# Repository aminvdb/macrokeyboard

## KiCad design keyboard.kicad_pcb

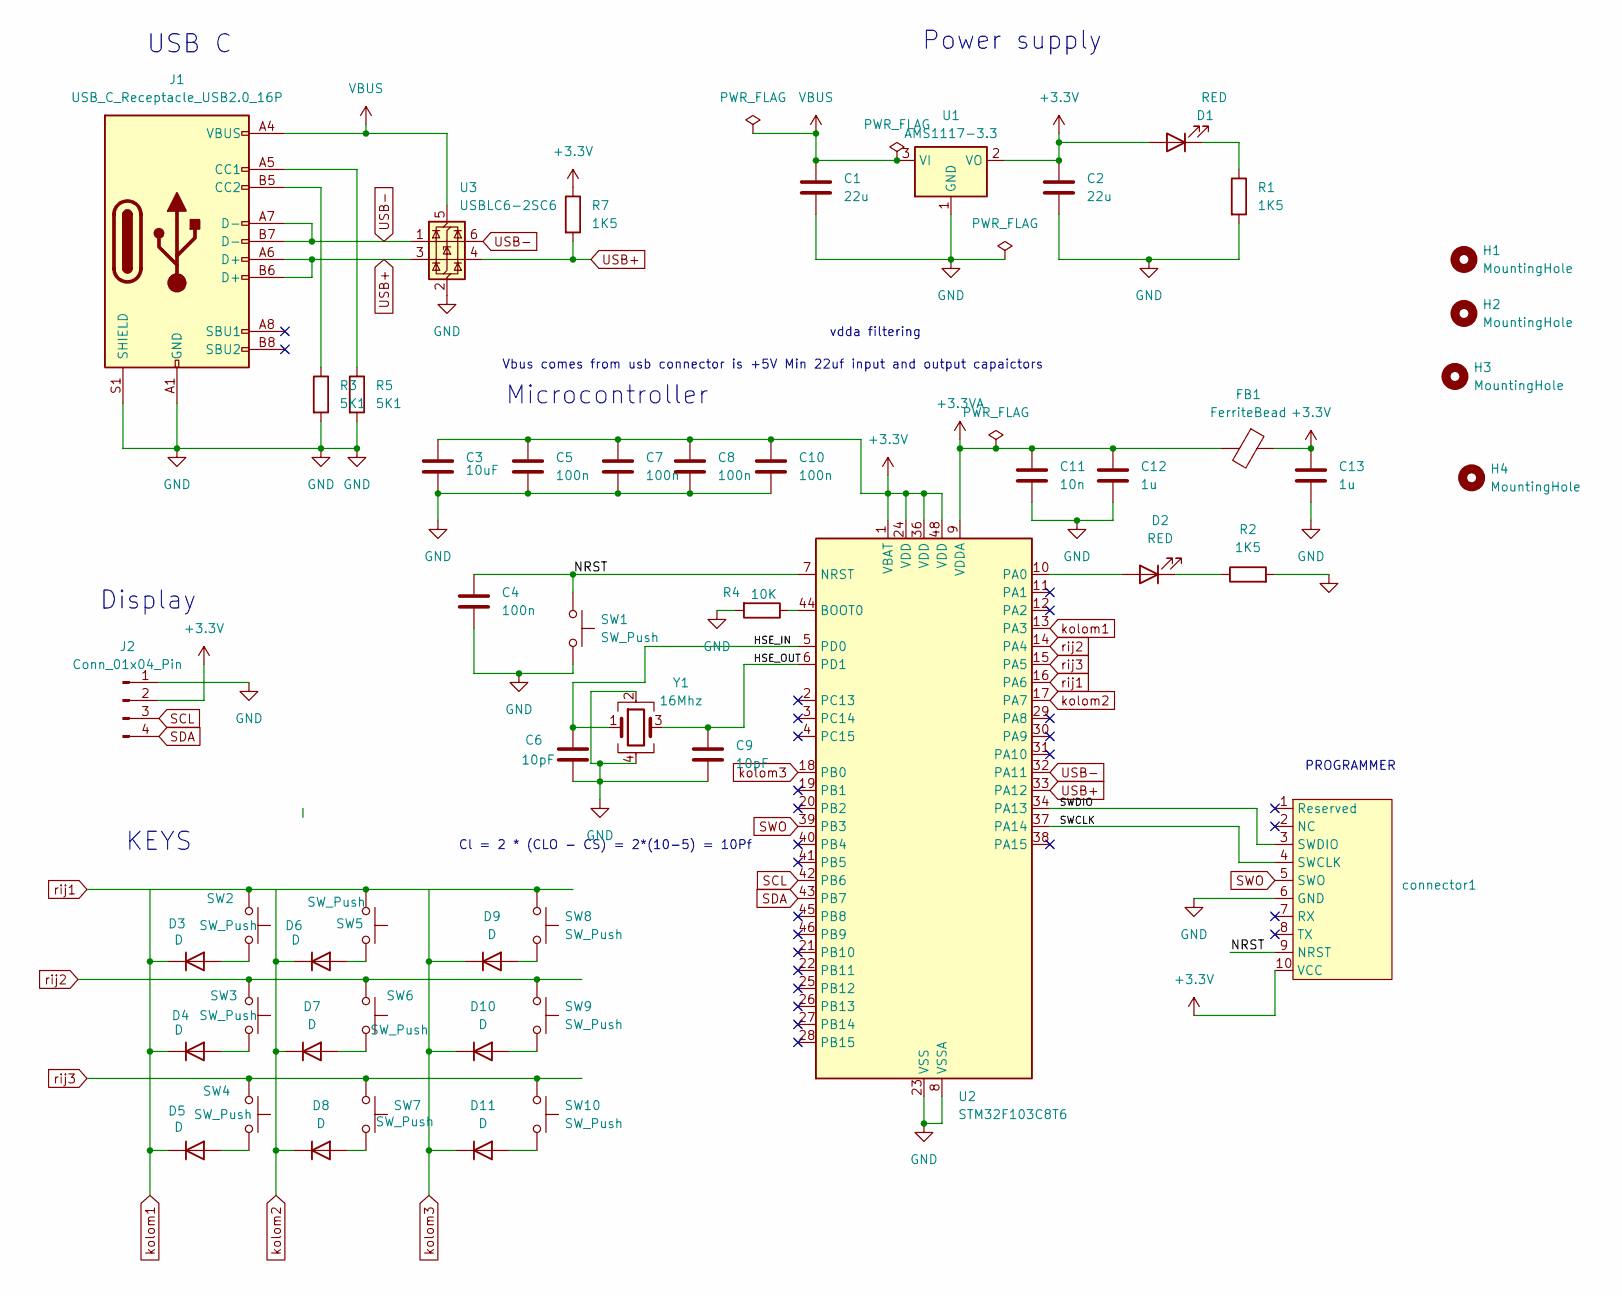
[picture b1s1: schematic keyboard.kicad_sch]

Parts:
C1, C2: 22u; C_0603_1608Metric
C3: 10uF; C_0603_1608Metric
C4, C5, C7, C8, C10: 100n; C_0603_1608Metric
C6, C9: 10pF; C_0603_1608Metric
C11: 10n; C_0603_1608Metric
C12, C13: 1u; C_0603_1608Metric
D1, D2: RED; LED_0603_1608Metric
D3, D4, D5, D6, D7, D8, D9, D10, D11: D; D_0603_1608Metric
FB1: FerriteBead; L_0603_1608Metric
H1, H2, H3, H4: MountingHole; MountingHole_2.1mm
J1: USB_C_Receptacle_USB2.0_16P; USB_C_Receptacle_GCT_USB4105-xx-A_16P_TopMnt_Horizontal
J2: Conn_01x04_Pin; PinHeader_1x04_P2.54mm_Vertical
R1, R2: 1K5; R_0402_1005Metric
R3, R5: 5K1; R_0603_1608Metric
R4: 10K; R_0603_1608Metric
R7: 1K5; R_0603_1608Metric
SW1: SW_Push; SW_SPST_TL3305B
SW2, SW3, SW4, SW5, SW6, SW7, SW8, SW9, SW10: SW_Push; Kailh_socket_MX
U1: AMS1117-3.3; SOT-223-3_TabPin2
U2: STM32F103C8T6; LQFP-48_7x7mm_P0.5mm
U3: USBLC6-2SC6; SOT-23-6
Y1: 16Mhz; Crystal_SMD_3225-4Pin_3.2x2.5mm
connector1: Open Ended Card Edge

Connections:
+3.3V: C2.1, C3.1, C5.1, C7.1, C8.1, C10.1, C13.1, D1.2 (A), FB1.1, J2.2, R7.1, U1.2 (VO), U2.1 (VBAT), U2.24 (VDD), U2.36 (VDD), U2.48 (VDD), connector1.10 (VCC)
+3.3VA: C11.1, C12.1, FB1.2, U2.9 (VDDA)
/HSE_IN: C6.1, U2.5 (PD0), Y1.1
/HSE_OUT: C9.1, U2.6 (PD1), Y1.3
/NRST: C4.1, SW1.1, U2.7 (NRST), connector1.9 (NRST)
/SWCLK: U2.37 (PA14), connector1.4 (SWCLK)
/SWDIO: U2.34 (PA13), connector1.3 (SWDIO)
GND: C1.2, C2.2, C3.2, C4.2, C5.2, C6.2, C7.2, C8.2, C9.2, C10.2, C11.2, C12.2, C13.2, J1.A1 (GND), J1.A12 (GND), J1.B1 (GND), J1.B12 (GND), J1.S1 (SHIELD), J2.1, R1.2, R2.2, R3.2, R4.2, R5.2, SW1.2, U1.1 (GND), U2.8 (VSSA), U2.23 (VSS), U2.35 (VSS), U2.47 (VSS), U3.2 (GND), Y1.2, Y1.4, connector1.6 (GND)
unnamed: D1.1 (K), R1.1
unnamed: D2.2 (A), U2.10 (PA0)
unnamed: D2.1 (K), R2.1
unnamed: D3.2 (A), SW2.2
unnamed: D4.2 (A), SW3.2
unnamed: D5.2 (A), SW4.2
unnamed: D6.2 (A), SW5.2
unnamed: D7.2 (A), SW6.2
unnamed: D8.2 (A), SW7.2
unnamed: D9.2 (A), SW8.2
unnamed: D10.2 (A), SW9.2
unnamed: D11.2 (A), SW10.2
unnamed: J1.A5 (CC1), R5.1
unnamed: J1.B5 (CC2), R3.1
unnamed: R4.1, U2.44 (BOOT0)
SCL: J2.3, U2.42 (PB6)
SDA: J2.4, U2.43 (PB7)
SWO: U2.39 (PB3), connector1.5 (SWO)
USB+: J1.A6 (D+), J1.B6 (D+), R7.2, U2.33 (PA12), U3.3 (I/O2), U3.4 (I/O2)
USB-: J1.A7 (D-), J1.B7 (D-), U2.32 (PA11), U3.1 (I/O1), U3.6 (I/O1)
VBUS: C1.1, J1.A4 (VBUS), J1.A9 (VBUS), J1.B4 (VBUS), J1.B9 (VBUS), U1.3 (VI), U3.5 (VBUS)
kolom1: D3.1 (K), D4.1 (K), D5.1 (K), U2.13 (PA3)
kolom2: D6.1 (K), D7.1 (K), D8.1 (K), U2.17 (PA7)
kolom3: D9.1 (K), D10.1 (K), D11.1 (K), U2.18 (PB0)
rij1: SW2.1, SW5.1, SW8.1, U2.16 (PA6)
rij2: SW3.1, SW6.1, SW9.1, U2.14 (PA4)
rij3: SW4.1, SW7.1, SW10.1, U2.15 (PA5)

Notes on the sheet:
KEYS
Power supply
Cl = 2 * (CLO - CS) = 2*(10-5) = 10Pf
vdda filtering
PROGRAMMER
USB C
Vbus comes from usb connector is +5V Min 22uf input and output capaictors
Microcontroller
Display

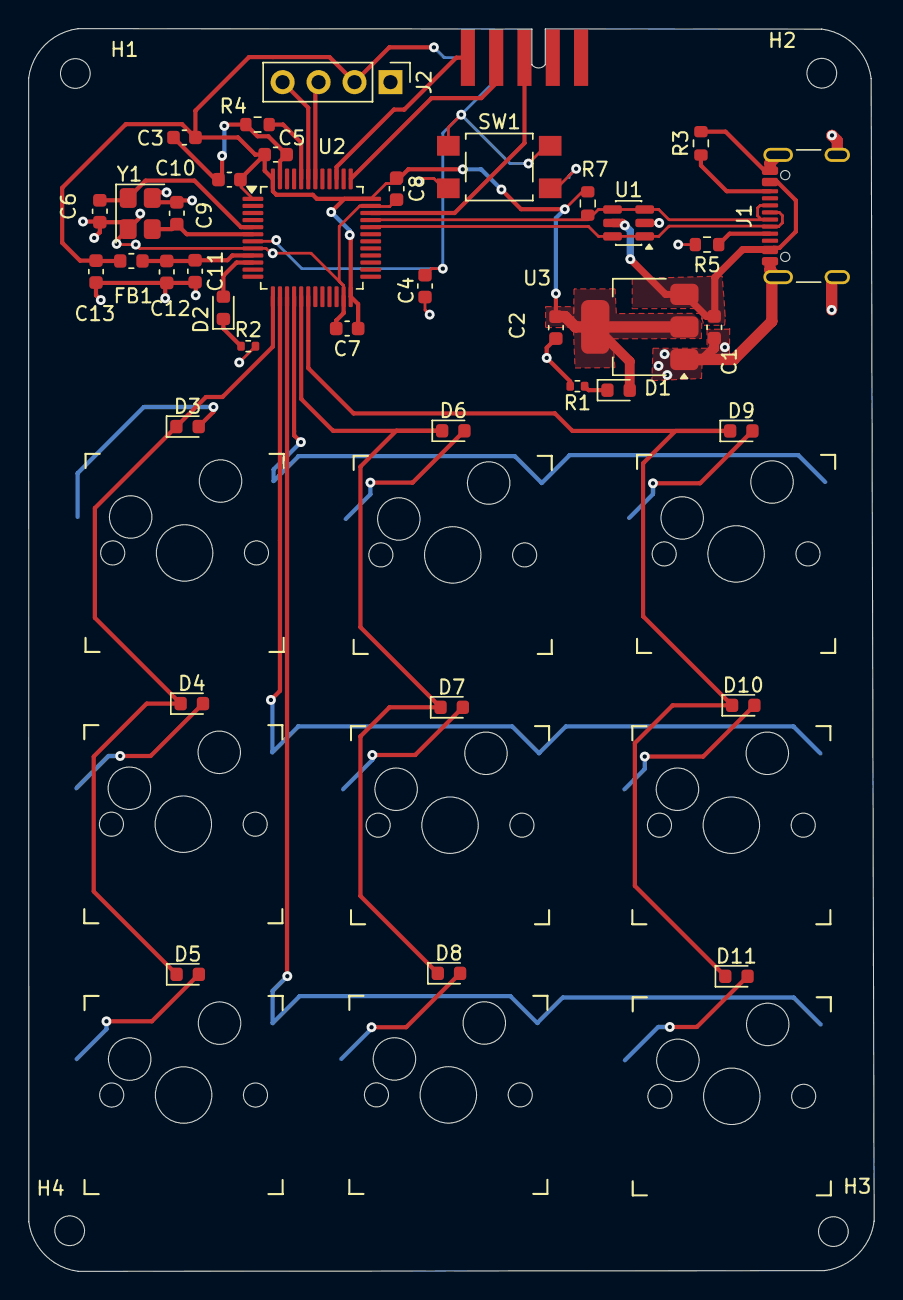
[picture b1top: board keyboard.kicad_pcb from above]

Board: 2 copper layers, 59.7 x 87.8 mm, 53 parts (0 on the bottom side), 35 nets.

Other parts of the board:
H3#2: MountingHole; MountingHole_2.1mm

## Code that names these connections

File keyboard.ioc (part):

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Mcu.Name=STM32F103C(8-B)Tx
Mcu.Package=LQFP48
Mcu.UserName=STM32F103C8Tx
PA11.Mode=Device
PA11.Signal=USB_DM
PA12.Mode=Device
PA12.Signal=USB_DP
PA13.Mode=Trace_Asynchronous_SW
PA13.Signal=SYS_JTMS-SWDIO
PA14.Mode=Trace_Asynchronous_SW
PA14.Signal=SYS_JTCK-SWCLK
PA3.GPIOParameters=GPIO_Label
PA3.GPIO_Label=kolom1
PA3.Signal=GPIO_Output
PA4.GPIOParameters=GPIO_PuPd,GPIO_Label
PA4.GPIO_Label=rij2
PA4.GPIO_PuPd=GPIO_PULLUP
PA4.Signal=GPIO_Input
PA5.GPIOParameters=GPIO_PuPd,GPIO_Label
PA5.GPIO_Label=rij3
PA5.GPIO_PuPd=GPIO_PULLUP
PA5.Signal=GPIO_Input
PA6.GPIOParameters=GPIO_PuPd,GPIO_Label
PA6.GPIO_Label=rij1
PA6.GPIO_PuPd=GPIO_PULLUP
PA6.Signal=GPIO_Input
PA7.GPIOParameters=GPIO_Label
PA7.GPIO_Label=kolom2
PA7.Signal=GPIO_Output
PB0.GPIOParameters=GPIO_Label
PB0.GPIO_Label=kolom3
PB0.Signal=GPIO_Output
PB3.Mode=Trace_Asynchronous_SW
PB3.Signal=SYS_JTDO-TRACESWO
PB6.Mode=I2C
PB6.Signal=I2C1_SCL
PB7.Mode=I2C
PB7.Signal=I2C1_SDA
PC14-OSC32_IN.Mode=LSE-External-Oscillator
PC14-OSC32_IN.Signal=RCC_OSC32_IN
PC15-OSC32_OUT.Mode=LSE-External-Oscillator
PC15-OSC32_OUT.Signal=RCC_OSC32_OUT
PD0-OSC_IN.Mode=HSE-External-Oscillator
PD0-OSC_IN.Signal=RCC_OSC_IN
PD1-OSC_OUT.Mode=HSE-External-Oscillator
PD1-OSC_OUT.Signal=RCC_OSC_OUT
RCC.HSEDivPLL=RCC_HSE_PREDIV_DIV2
RCC.HSE_VALUE=16000000
RCC.SYSCLKFreq_VALUE=72000000
RCC.SYSCLKSource=RCC_SYSCLKSOURCE_PLLCLK
board=custom
